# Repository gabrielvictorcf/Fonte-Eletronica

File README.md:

# Fonte-Eletronica
Esquemáticos e explicação da fonte desenvolvida em Eletrônica para Computação

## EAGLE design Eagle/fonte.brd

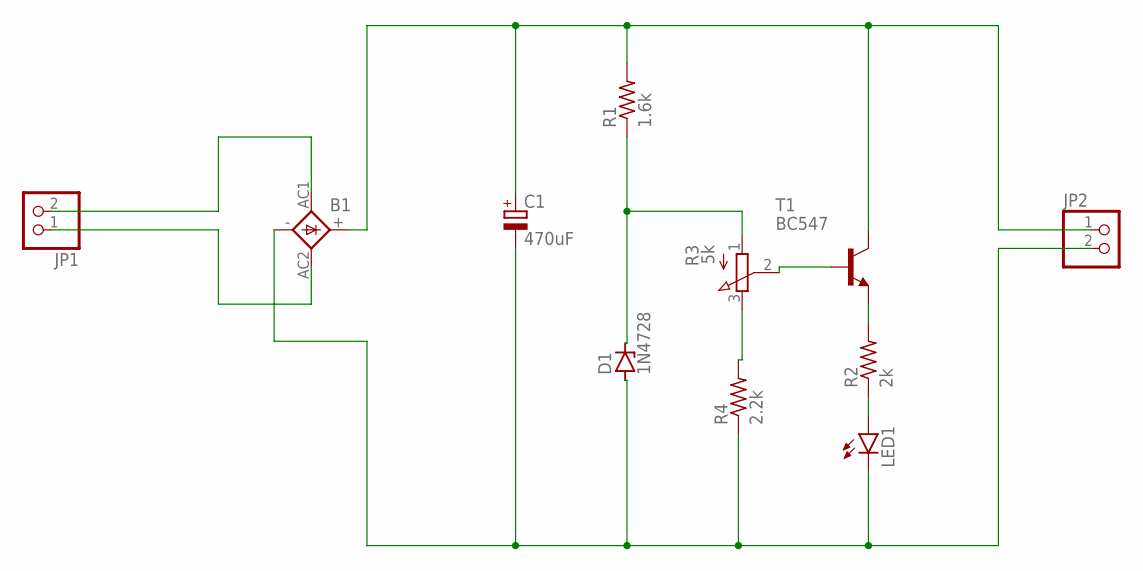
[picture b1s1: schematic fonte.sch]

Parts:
B1: 1KAB
C1: 470uF; E5-10,5
D1: 1N4728; DO41Z10
JP1, JP2: PINHD-1X2; 1X02
LED1: LED5MM
R1: 1.6k; 0207/10
R2: 2k; 0207/10
R3: 5k; 3RP/1610N
R4: 2.2k; 0207/10
T1: BC547; TO92

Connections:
unnamed: B1.AC1, JP1.2
unnamed: B1.AC2, JP1.1
unnamed: B1.+, C1.+, JP2.1, R1.2, T1.3 (C)
unnamed: B1.-, C1.-, D1.A, JP2.2, LED1.K (C), R4.1
unnamed: D1.C, R1.1, R3.1 (A)
unnamed: R3.3 (E), R4.2
unnamed: R3.2 (S), T1.2 (B)
unnamed: R2.2, T1.1 (E)
unnamed: LED1.A, R2.1

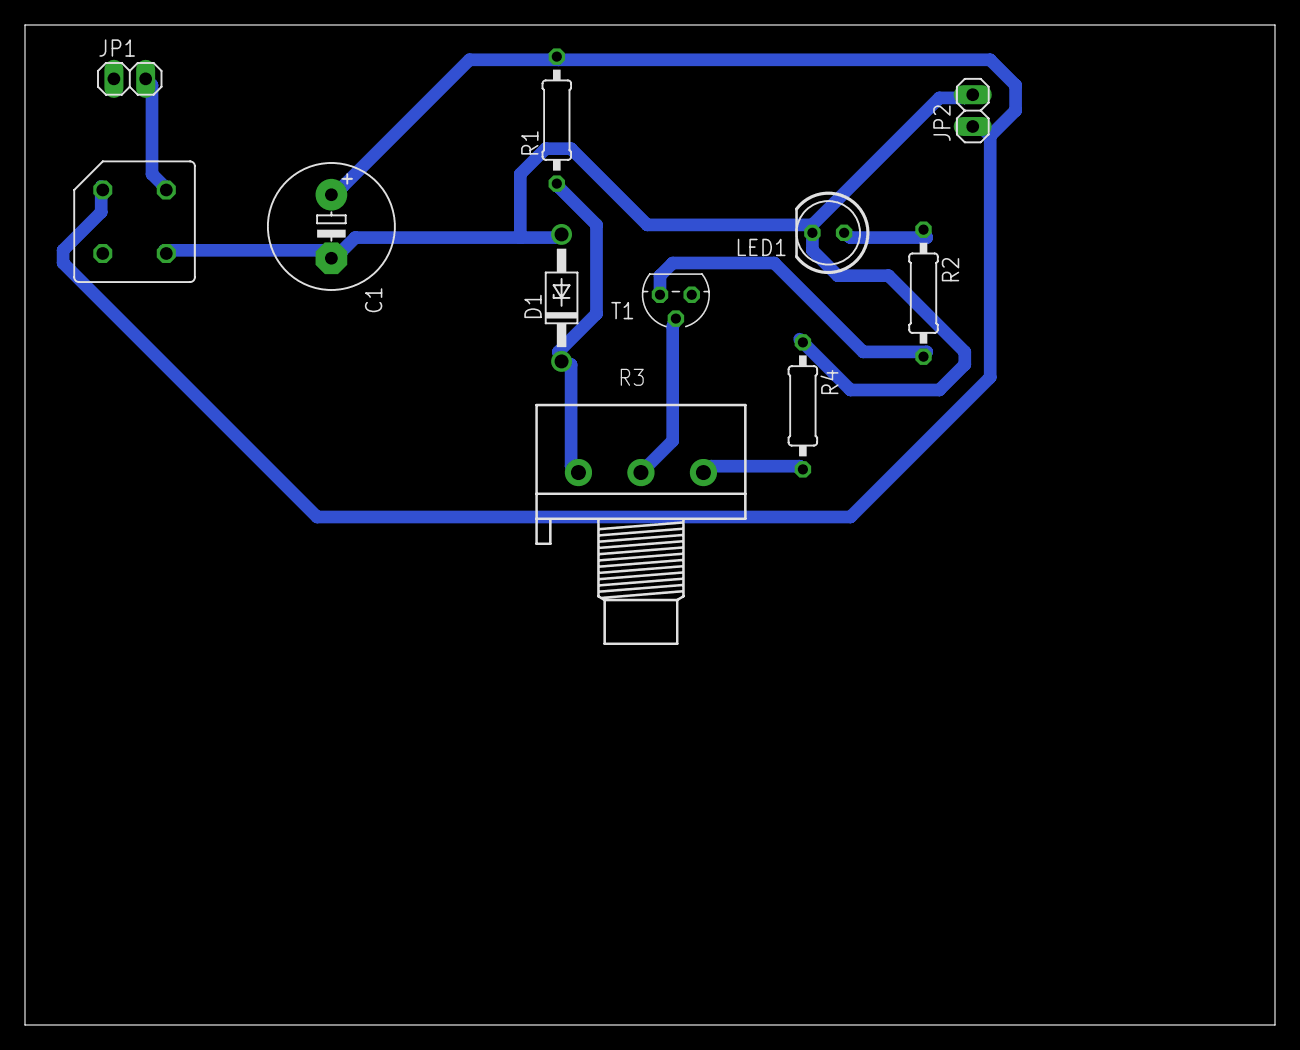
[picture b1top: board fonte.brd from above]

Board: 2 copper layers, 100.0 x 80.0 mm, 11 parts (0 on the bottom side), 9 nets.

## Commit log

2020-07-07 add Falstad simu add circuit walkthrough
2020-07-09 Create PCB
2020-07-09 add Ponte Retificadora
2020-07-09 add video explicando circuito
2020-07-09 fix video pic/link
2020-07-09 fix "Explicação do circuito[...]" on ReadMe
